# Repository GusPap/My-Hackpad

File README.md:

# My-Hackpad

## Project Description
My project is a custom macropad designed with KiCad and Autodesk Fusion, and programmed with KMK Firmware. 

### How I'll use it:
I'm setting this up to handle my daily shortcuts.
 One-tap to open Spotify and play/pause my playlists.
 I’m mapping keys to open my most-used apps like my browser or my code editor instantly.
 Simple things like "Mute/Unmute" or "Screenshot" that are usually awkward to do on a laptop keyboard.

### Why I made this:
My friends told me about Hack Club Blueprint and suggested I do a guided project since I was a complete beginner. I found the macropad interesting and challenged myself to build a piece of hardware with no prior experience to see if I could do it!
### Project Gallery

#### Circuit Schematic

#### PCB Layout (2D & 3D)

#### Case

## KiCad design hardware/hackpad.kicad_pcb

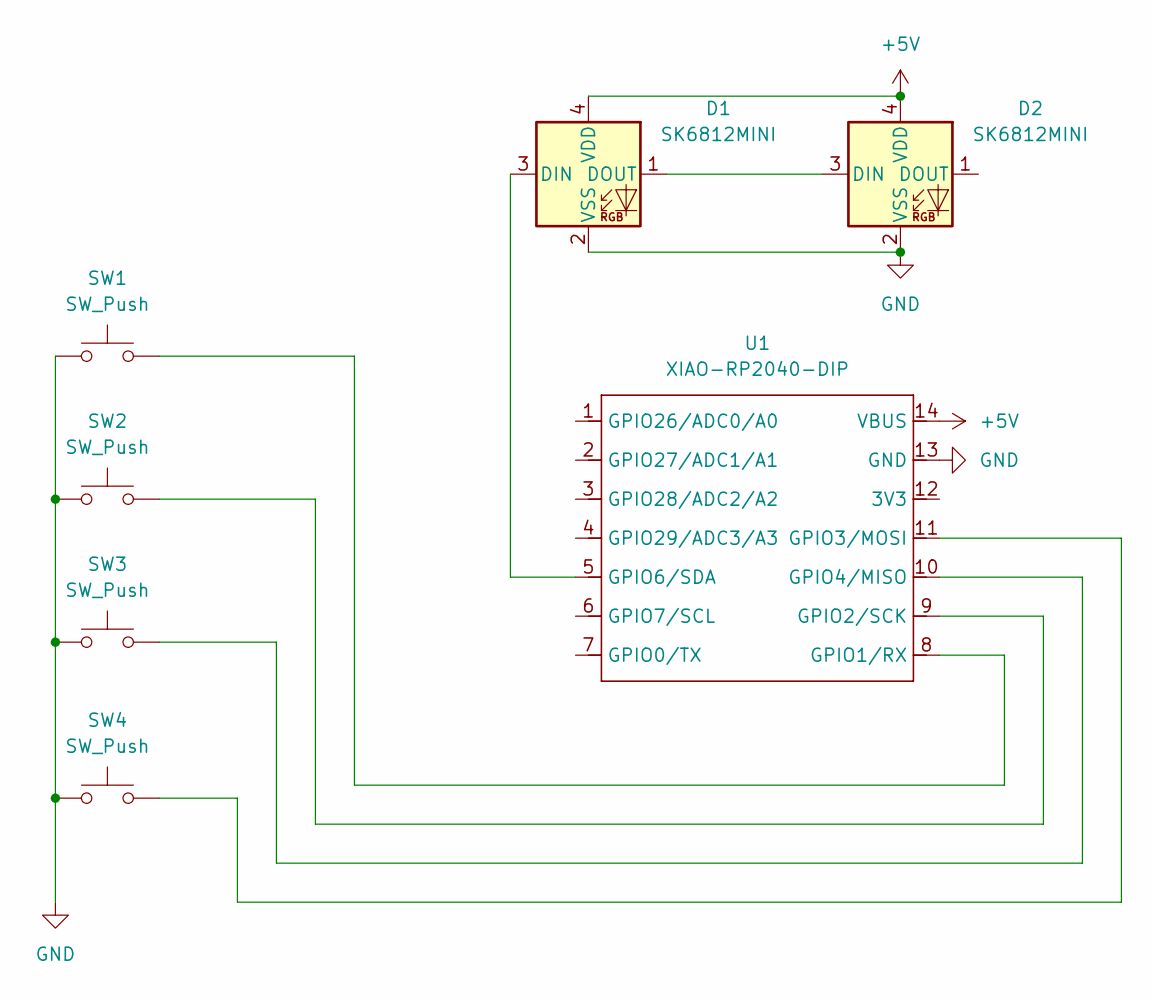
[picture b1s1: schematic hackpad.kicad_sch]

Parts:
D1, D2: SK6812MINI; LED_SK6812MINI_PLCC4_3.5x3.5mm_P1.75mm
SW1, SW2, SW3, SW4: SW_Push; SW_Cherry_MX_1.00u_PCB
U1: XIAO-RP2040-DIP

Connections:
+5V: D1.4 (VDD), D2.4 (VDD), U1.14 (VBUS)
GND: D1.2 (VSS), D2.2 (VSS), SW1.1, SW2.1, SW3.1, SW4.1, U1.13 (GND)
unnamed: D1.3 (DIN), U1.5 (GPIO6/SDA)
unnamed: D1.1 (DOUT), D2.3 (DIN)
unnamed: SW1.2, U1.8 (GPIO1/RX)
unnamed: SW2.2, U1.9 (GPIO2/SCK)
unnamed: SW4.2, U1.11 (GPIO3/MOSI)
unnamed: SW3.2, U1.10 (GPIO4/MISO)

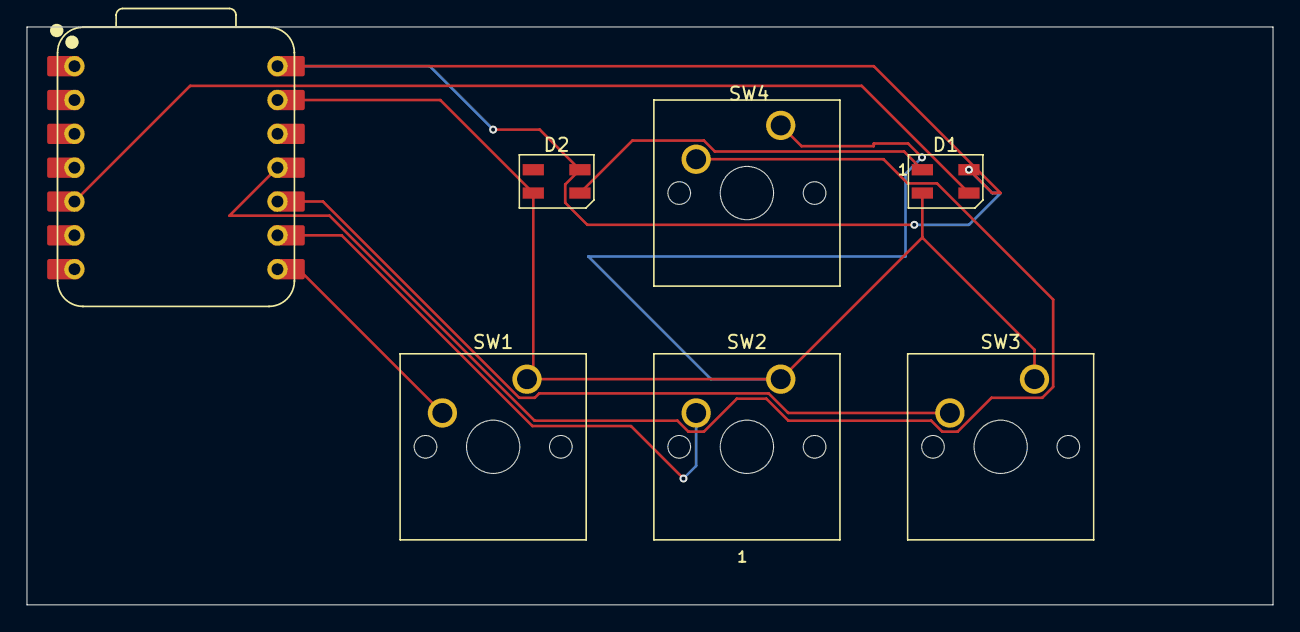
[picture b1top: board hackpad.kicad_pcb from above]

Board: 2 copper layers, 93.5 x 43.4 mm, 7 parts (0 on the bottom side), 8 nets.

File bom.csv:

Reference,Value,Footprint,Quantity
U1,XIAO-RP2040-DIP,Seeed XIAO RP2040,1
D1,SK6812MINI,SK6812MINI,1
D2,SK6812MINI,SK6812MINI,1
SW1,MX-Style Switch,SW_Push,1
SW2,MX-Style Switch,SW_Push,1
SW3,MX-Style Switch,SW_Push,1
SW4,MX-Style Switch,SW_Push,1
KC1,MX-Style Keycap,Keycap_1U,1
KC2,MX-Style Keycap,Keycap_1U,1
KC3,MX-Style Keycap,Keycap_1U,1
KC4,MX-Style Keycap,Keycap_1U,1

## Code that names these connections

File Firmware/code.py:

# code.py — KMK Firmware for Hackpad
# Hardware: XIAO RP2040, 4x switches, 2x SK6812MINI LEDs

import board
import neopixel

from kmk.kmk_keyboard import KMKKeyboard
from kmk.scanners.keypad import KeysScanner
from kmk.keys import KC
from kmk.modules.macros import Press, Release, Tap, Macros, Delay

# ── Keyboard ───────────────────────────────────────────────────────
keyboard = KMKKeyboard()

macros = Macros()
keyboard.modules.append(macros)

# ── Switches ───────────────────────────────────────────────────────
# SW1 → GPIO1 | SW2 → GPIO2 | SW3 → GPIO4 | SW4 → GPIO3
PINS = [board.D1, board.D2, board.D4, board.D3]

keyboard.matrix = KeysScanner(
    pins=PINS,
    value_when_pressed=False,
)

# ── LEDs ───────────────────────────────────────────────────────────
# 2x SK6812MINI chained, data on GPIO6
pixels = neopixel.NeoPixel(
    board.D6,
    2,
    brightness=0.3,
    auto_write=True, # Changed to True so it actively manages the LEDs
    pixel_order=neopixel.GRBW
)
pixels[0] = (255, 0, 128, 0)
pixels[1] = (0, 128, 255, 0)

# ── Keymap ─────────────────────────────────────────────────────────
# SW1 → Open Google Chrome (Windows)
# SW2 → Open Spotify (Windows)
# SW3 → Copy  (Ctrl+C)
# SW4 → Paste (Ctrl+V)

keyboard.keymap = [
    [
        # Chrome Macro (Added 100ms delay for the Run window to open)
        KC.MACRO(
            Press(KC.LGUI), Tap(KC.R), Release(KC.LGUI),
            Delay(100),
            Tap(KC.C), Tap(KC.H), Tap(KC.R), Tap(KC.O), Tap(KC.M), Tap(KC.E),
            Tap(KC.ENTER)
        ),

        # Spotify Macro (Added 100ms delay for the Run window to open)
        KC.MACRO(
            Press(KC.LGUI), Tap(KC.R), Release(KC.LGUI),
            Delay(100),
            Tap(KC.S), Tap(KC.P), Tap(KC.O), Tap(KC.T), Tap(KC.I), Tap(KC.F), Tap(KC.Y),
            Tap(KC.ENTER)
        ),

        # Optimized clean shortcuts instead of multi-line macros
        KC.LCTL(KC.C), # Ctrl + C
        KC.LCTL(KC.V), # Ctrl + V
    ]
]

# ── Run ────────────────────────────────────────────────────────────
if __name__ == '__main__':
    keyboard.go()

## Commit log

2026-03-29 Update README with project details and usage
    Added project description and usage details for the macropad.
2026-03-29 Create hardware
2026-03-29 Create images
2026-03-29 Create THings
2026-03-29 Create
2026-03-31 Create what??
2026-03-31 Create okok
2026-03-31 Rename
